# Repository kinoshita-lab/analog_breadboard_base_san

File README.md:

# Analog Breadboard Base san

[日本語](README.ja.md)

You have two cows. You want to build analog circuit with both positive/negative rails...

Here it is!

## Features

- USB PD supported. Use 15V if the PD power source if available
- When not, internal DC-DC can supply 15V(with a limited power which USB port can supply)
  - Confirmed working with M2 Macbook Air and Chuwi Freebook(meaning you can use this board with normal USB type-C port on your PC)
- Has 15V(unregulated) and -15V(unregulated) test point for the convinience of advanced users..

## Kit Contents

- Pre-assembled circuit board
- 2x2 pin socket connector(4 pcs.)
- 2x40 pin socket connector(2 pcs.)
- 2x20 pin socket connector(2 pcs.)

## What you will need

- USB Type-C Adapter(PD 15V supported)
- 2mm flat head screwdriver
- Multimeter

## How to assemble

- Solder the included connectors to the appropriate places on the circuit board.
- Connect USB Type-C adapter to the PCB and adjust both +12 and -12 potentiometer with screwdriver.

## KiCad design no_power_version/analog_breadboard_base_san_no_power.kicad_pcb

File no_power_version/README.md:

# GND Enhanced Breadboard Base chan

[日本語](README.ja.md)

## Kit Contents

- Print circuit board
- 2x2 pin socket connector(4 pcs.)
- 2x40 pin socket connector(2 pcs.)
- 2x20 pin socket connector(2 pcs.)

## What you will need

- Appropriate Power Source

## How to assemble

- Solder the included connectors to the appropriate places on the circuit board.

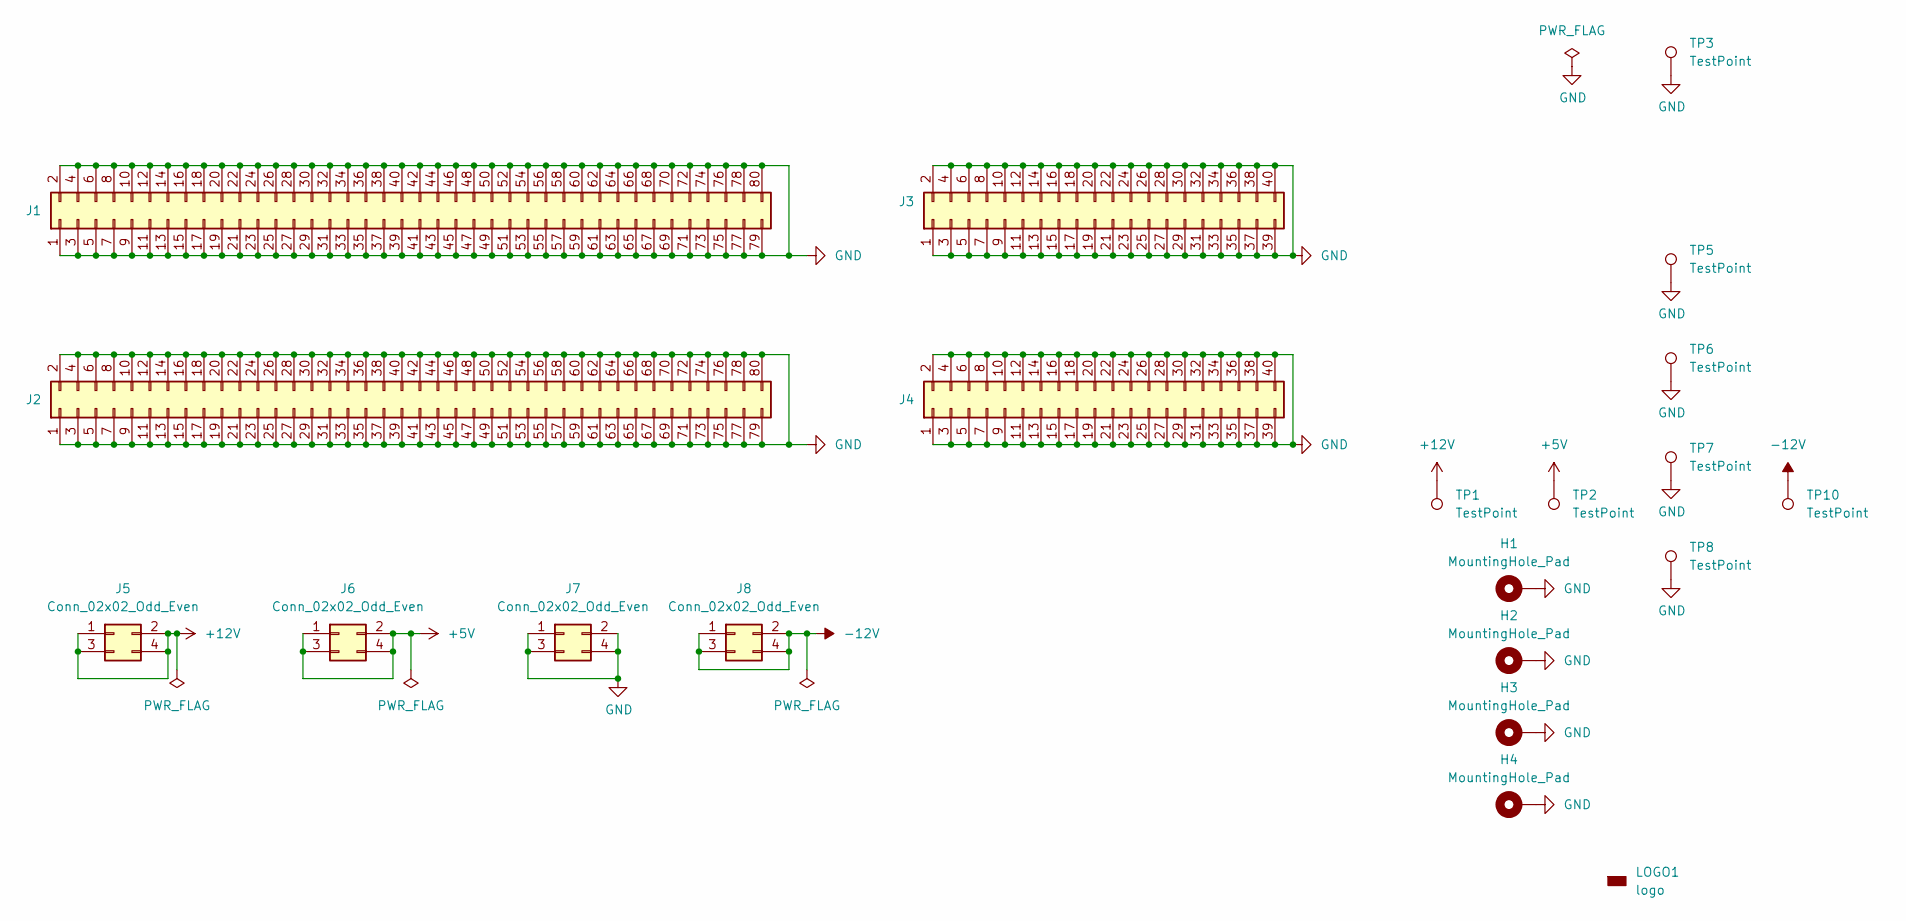
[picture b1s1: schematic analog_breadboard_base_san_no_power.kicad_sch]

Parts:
H1, H2, H3, H4: MountingHole_Pad; MountingHole_3.2mm_M3_DIN965_Pad
J1, J2: Conn_02x40_Odd_Even; PinSocket_2x40_P2.54mm_Vertical; LCSC C343637
J3, J4: Conn_02x20_Odd_Even; PinSocket_2x20_P2.54mm_Vertical; LCSC C2977589
J5, J6, J7, J8: Conn_02x02_Odd_Even; PinSocket_2x02_P2.54mm_Vertical; LCSC C2977590
LOGO1: logo; kinoshita-logo_simplified_300dpi
TP1, TP2, TP3, TP10: TestPoint; TP_PAD_WITH_HOLE
TP5, TP6, TP7, TP8: TestPoint; TP_PAD_LARGE

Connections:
+5V: J6.1, J6.2, J6.3, J6.4, TP2.1
+12V: J5.1, J5.2, J5.3, J5.4, TP1.1
-12V: J8.1, J8.2, J8.3, J8.4, TP10.1
GND: H1.1, H2.1, H3.1, H4.1, J1.1, J1.2, J1.3, J1.4, J1.5, J1.6, J1.7, J1.8, J1.9, J1.10, J1.11, J1.12, J1.13, J1.14, J1.15, J1.16, J1.17, J1.18, J1.19, J1.20, J1.21, J1.22, J1.23, J1.24, J1.25, J1.26, J1.27, J1.28, J1.29, J1.30, J1.31, J1.32, J1.33, J1.34, J1.35, J1.36, J1.37, J1.38, J1.39, J1.40, J1.41, J1.42, J1.43, J1.44, J1.45, J1.46, J1.47, J1.48, J1.49, J1.50, J1.51, J1.52, J1.53, J1.54, J1.55, J1.56, J1.57, J1.58, J1.59, J1.60, J1.61, J1.62, J1.63, J1.64, J1.65, J1.66, J1.67, J1.68, J1.69, J1.70, J1.71, J1.72, J1.73, J1.74, J1.75, J1.76, J1.77, J1.78, J1.79, J1.80, J2.1, J2.2, J2.3, J2.4, J2.5, J2.6, J2.7, J2.8, J2.9, J2.10, J2.11, J2.12, J2.13, J2.14, J2.15, J2.16, J2.17, J2.18, J2.19, J2.20, J2.21, J2.22, J2.23, J2.24, J2.25, J2.26, J2.27, J2.28, J2.29, J2.30, J2.31, J2.32, J2.33, J2.34, J2.35, J2.36, J2.37, J2.38, J2.39, J2.40, J2.41, J2.42, J2.43, J2.44, J2.45, J2.46, J2.47, J2.48, J2.49, J2.50, J2.51, J2.52, J2.53, J2.54, J2.55, J2.56, J2.57, J2.58, J2.59, J2.60, J2.61, J2.62, J2.63, J2.64, J2.65, J2.66, J2.67, J2.68, J2.69, J2.70, J2.71, J2.72, J2.73, J2.74, J2.75, J2.76, J2.77, J2.78, J2.79, J2.80, J3.1, J3.2, J3.3, J3.4, J3.5, J3.6, J3.7, J3.8, J3.9, J3.10, J3.11, J3.12, J3.13, J3.14, J3.15, J3.16, J3.17, J3.18, J3.19, J3.20, J3.21, J3.22, J3.23, J3.24, J3.25, J3.26, J3.27, J3.28, J3.29, J3.30, J3.31, J3.32, J3.33, J3.34, J3.35, J3.36, J3.37, J3.38, J3.39, J3.40, J4.1, J4.2, J4.3, J4.4, J4.5, J4.6, J4.7, J4.8, J4.9, J4.10, J4.11, J4.12, J4.13, J4.14, J4.15, J4.16, J4.17, J4.18, J4.19, J4.20, J4.21, J4.22, J4.23, J4.24, J4.25, J4.26, J4.27, J4.28, J4.29, J4.30, J4.31, J4.32, J4.33, J4.34, J4.35, J4.36, J4.37, J4.38, J4.39, J4.40, J7.1, J7.2, J7.3, J7.4, TP3.1, TP5.1, TP6.1, TP7.1, TP8.1

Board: 2 copper layers, 21 parts (1 on the bottom side), 4 nets, no tracks yet.

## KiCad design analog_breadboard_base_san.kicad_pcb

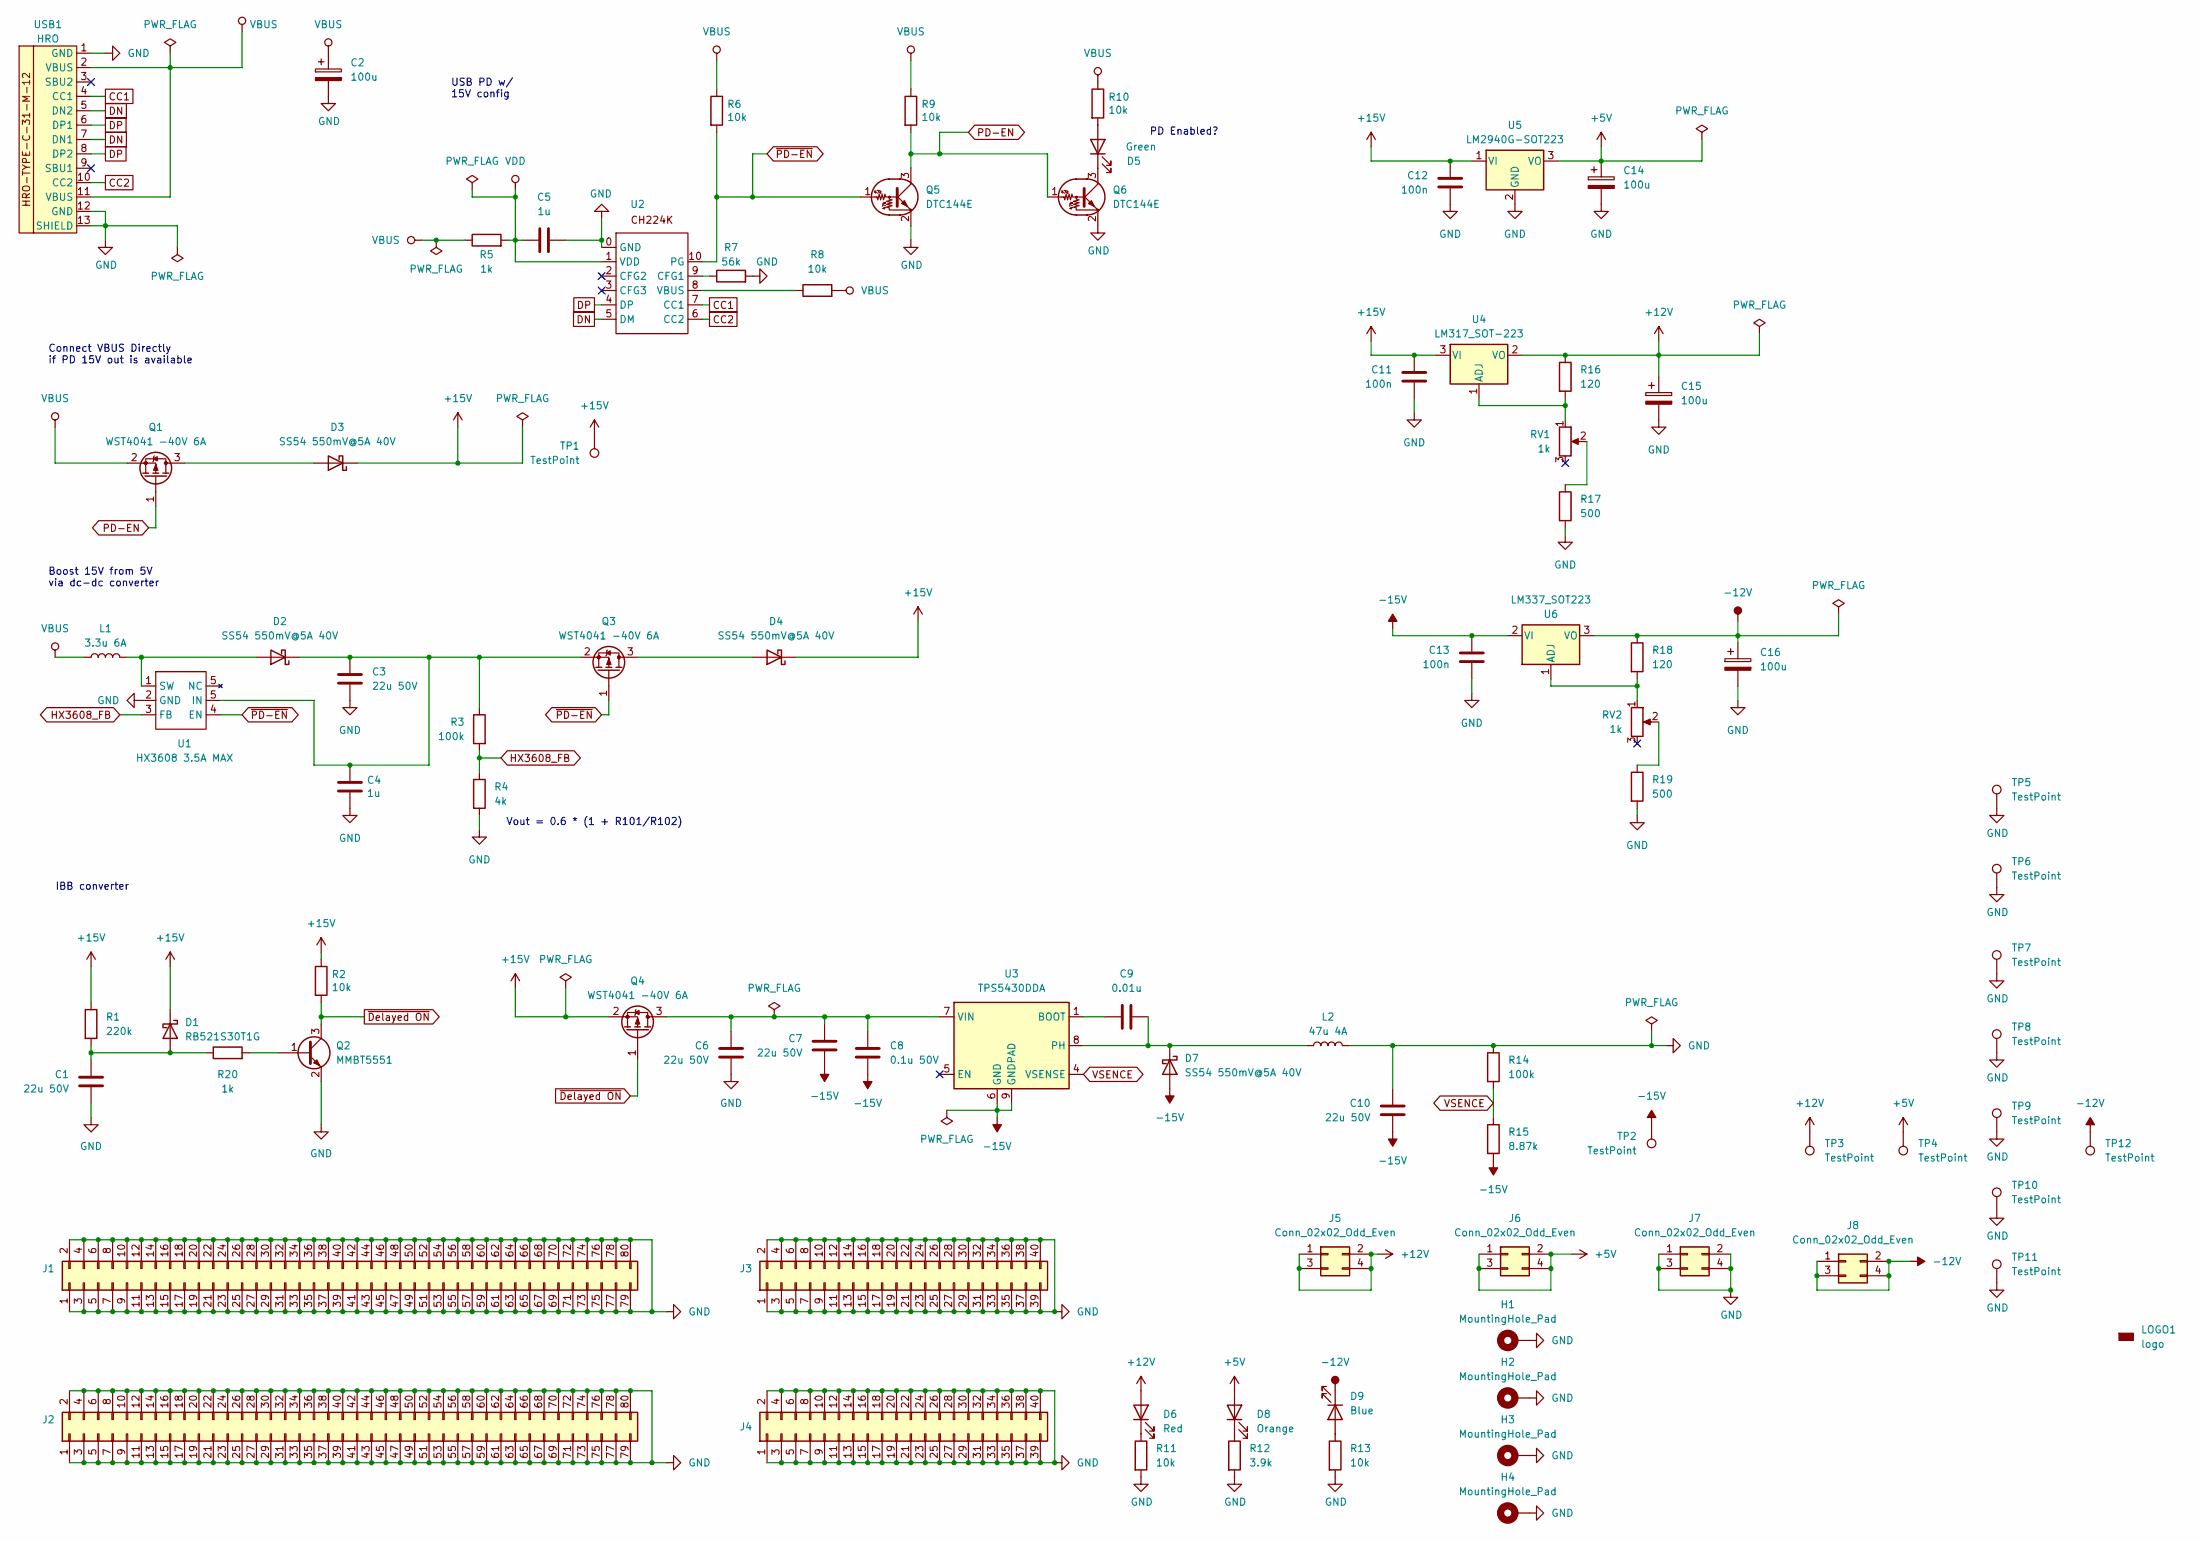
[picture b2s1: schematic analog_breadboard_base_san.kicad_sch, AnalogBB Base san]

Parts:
C1, C6, C7, C10: 22u 50V; C0805; LCSC C22367832
C2, C14, C15, C16: 100u; CP_Elec_6.3x5.4; LCSC C72478
C3: 22u 50V; C0603; LCSC C22367832
C4, C5: 1u; C0402; LCSC C14445
C8: 0.1u 50V; C0603; LCSC C1591
C9: 0.01u; C0603; LCSC C387983
C11, C12, C13: 100n; C0402; LCSC C56392
D1: RB521S30T1G; D_SOD-523; LCSC C145179
D2, D3, D4, D7: SS54 550mV@5A 40V; D_SMA; LCSC C727065
D5: Green; LED_0402_1005Metric_Enhanced_Cathode; LCSC C434449
D6: Red; LED_0402_1005Metric_Enhanced_Cathode; LCSC C434445
D8: Orange; LED_0402_1005Metric_Enhanced_Cathode; LCSC C965791
D9: Blue; LED_0402_1005Metric_Enhanced_Cathode; LCSC C434447
H1, H2, H3, H4: MountingHole_Pad; MountingHole_3.2mm_M3_DIN965_Pad
J1, J2: Conn_02x40_Odd_Even; PinSocket_2x40_P2.54mm_Vertical; LCSC C343637
J3, J4: Conn_02x20_Odd_Even; PinSocket_2x20_P2.54mm_Vertical; LCSC C2977589
J5, J6, J7, J8: Conn_02x02_Odd_Even; PinSocket_2x02_P2.54mm_Vertical; LCSC C2977590
L1: 3.3u 6A; Inductor_SMD_5.2x5.7; LCSC C2847476
L2: 47u 4A; Inductor_SMD_11.5x10.5; LCSC C20415550
LOGO1: logo; kinoshita-logo_simplified_300dpi
Q1, Q3, Q4: WST4041 -40V 6A; SOT-23; LCSC C148357
Q2: MMBT5551; SOT-23; LCSC C2145
Q5, Q6: DTC144E; SOT-523; LCSC C242410
R1: 220k; R_0402_1005Metric; LCSC C25767
R2, R6, R8, R9, R10, R11, R13: 10k; R_0402_1005Metric; LCSC C25744
R3: 100k; R_0402_1005Metric; LCSC C60491
R4: 4k; R_0402_1005Metric; LCSC C51721
R5, R20: 1k; R_0402_1005Metric; LCSC C11702
R7: 56k; R_0402_1005Metric; LCSC C25796
R12: 3.9k; R_0402_1005Metric; LCSC C51721
R14: 100k; R_0402_1005Metric; LCSC C25530
R15: 8.87k; R_0402_1005Metric; LCSC C155696
R16, R18: 120; R_0402_1005Metric; LCSC C25079
R17, R19: 500; R_0402_1005Metric; LCSC C25167
RV1, RV2: 1k; POT_BOCHEN 3296W C118963; LCSC C118949
TP1, TP2, TP3, TP4, TP5, TP12: TestPoint; TP_PAD_WITH_HOLE
TP6, TP7, TP8, TP9, TP10, TP11: TestPoint; TP_PAD_LARGE
U1: HX3608 3.5A MAX; SOT-23-6; LCSC C296278
U2: CH224K; ESSOP-10_3.9x4.9mm_P1.00mm; LCSC C970725
U3: TPS5430DDA; TI_SO-PowerPAD-8_ThermalVias; LCSC C9864
U4: LM317_SOT-223; SOT-223-3_TabPin2; LCSC C347367
U5: LM2940G-SOT223; SOT-223-3_TabPin2; LCSC C71094
U6: LM337_SOT223; SOT-223-3_TabPin2; LCSC C527400
USB1: HRO; Conn USB TYPE-C16P3MDDGP073 C2965608; LCSC C2965608

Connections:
+5V: C14.1, D8.2 (A), J6.1, J6.2, J6.3, J6.4, TP4.1, U5.3 (VO)
+12V: C15.1, D6.2 (A), J5.1, J5.2, J5.3, J5.4, R16.1, TP3.1, U4.2 (VO)
+15V: C11.2, C12.2, D1.1 (K), D3.1 (K), D4.1 (K), Q4.2 (S), R1.1, R2.1, TP1.1, U4.3 (VI), U5.1 (VI)
-12V: C16.1, D9.1 (K), J8.1, J8.2, J8.3, J8.4, R18.1, TP12.1, U6.3 (VO)
-15V: C7.2, C8.1, C10.2, C13.2, D7.2 (A), R15.2, TP2.1, U3.6 (GND), U3.9 (GNDPAD), U6.2 (VI)
CC1: U2.7 (CC1), USB1.4 (CC1)
CC2: U2.6 (CC2), USB1.10 (CC2)
DN: U2.5 (DM), USB1.5 (DN2), USB1.7 (DN1)
DP: U2.4 (DP), USB1.6 (DP1), USB1.8 (DP2)
GND: C1.2, C2.2, C3.2, C4.2, C5.2, C6.2, C10.1, C11.1, C12.1, C13.1, C14.2, C15.2, C16.2, H1.1, H2.1, H3.1, H4.1, J1.1, J1.2, J1.3, J1.4, J1.5, J1.6, J1.7, J1.8, J1.9, J1.10, J1.11, J1.12, J1.13, J1.14, J1.15, J1.16, J1.17, J1.18, J1.19, J1.20, J1.21, J1.22, J1.23, J1.24, J1.25, J1.26, J1.27, J1.28, J1.29, J1.30, J1.31, J1.32, J1.33, J1.34, J1.35, J1.36, J1.37, J1.38, J1.39, J1.40, J1.41, J1.42, J1.43, J1.44, J1.45, J1.46, J1.47, J1.48, J1.49, J1.50, J1.51, J1.52, J1.53, J1.54, J1.55, J1.56, J1.57, J1.58, J1.59, J1.60, J1.61, J1.62, J1.63, J1.64, J1.65, J1.66, J1.67, J1.68, J1.69, J1.70, J1.71, J1.72, J1.73, J1.74, J1.75, J1.76, J1.77, J1.78, J1.79, J1.80, J2.1, J2.2, J2.3, J2.4, J2.5, J2.6, J2.7, J2.8, J2.9, J2.10, J2.11, J2.12, J2.13, J2.14, J2.15, J2.16, J2.17, J2.18, J2.19, J2.20, J2.21, J2.22, J2.23, J2.24, J2.25, J2.26, J2.27, J2.28, J2.29, J2.30, J2.31, J2.32, J2.33, J2.34, J2.35, J2.36, J2.37, J2.38, J2.39, J2.40, J2.41, J2.42, J2.43, J2.44, J2.45, J2.46, J2.47, J2.48, J2.49, J2.50, J2.51, J2.52, J2.53, J2.54, J2.55, J2.56, J2.57, J2.58, J2.59, J2.60, J2.61, J2.62, J2.63, J2.64, J2.65, J2.66, J2.67, J2.68, J2.69, J2.70, J2.71, J2.72, J2.73, J2.74, J2.75, J2.76, J2.77, J2.78, J2.79, J2.80, J3.1, J3.2, J3.3, J3.4, J3.5, J3.6, J3.7, J3.8, J3.9, J3.10, J3.11, J3.12, J3.13, J3.14, J3.15, J3.16, J3.17, J3.18, J3.19, J3.20, J3.21, J3.22, J3.23, J3.24, J3.25, J3.26, J3.27, J3.28, J3.29, J3.30, J3.31, J3.32, J3.33, J3.34, J3.35, J3.36, J3.37, J3.38, J3.39, J3.40, J4.1, J4.2, J4.3, J4.4, J4.5, J4.6, J4.7, J4.8, J4.9, J4.10, J4.11, J4.12, J4.13, J4.14, J4.15, J4.16, J4.17, J4.18, J4.19, J4.20, J4.21, J4.22, J4.23, J4.24, J4.25, J4.26, J4.27, J4.28, J4.29, J4.30, J4.31, J4.32, J4.33, J4.34, J4.35, J4.36, J4.37, J4.38, J4.39, J4.40, J7.1, J7.2, J7.3, J7.4, L2.2, Q2.2 (E), Q5.2 (E), Q6.2 (E), R4.2, R7.2, R11.2, R12.2, R13.2, R14.1, R17.2, R19.2, TP5.1, TP6.1, TP7.1, TP8.1, TP9.1, TP10.1, TP11.1, U1.2 (GND), U2.0 (GND), U5.2 (GND), USB1.1 (GND), USB1.12 (GND), USB1.13 (SHIELD)
HX3608_FB: R3.2, R4.1, U1.3 (FB)
unnamed: C1.1, D1.2 (A), R1.2, R20.1
unnamed: D2.2 (A), L1.2, U1.1 (SW)
unnamed: C3.1, C4.1, D2.1 (K), Q3.2 (S), R3.1, U1.5 (IN)
unnamed: D3.2 (A), Q1.3 (D)
unnamed: D4.2 (A), Q3.3 (D)
unnamed: D5.2 (A), R10.2
unnamed: D5.1 (K), Q6.3 (C)
unnamed: D6.1 (K), R11.1
unnamed: C9.2, D7.1 (K), L2.1, U3.8 (PH)
unnamed: D8.1 (K), R12.1
unnamed: D9.2 (A), R13.1
unnamed: Q2.1 (B), R20.2
unnamed: C6.1, C7.1, C8.2, Q4.3 (D), U3.7 (VIN)
unnamed: R17.1, RV1.2
unnamed: R19.1, RV2.2
unnamed: R7.1, U2.9 (CFG1)
unnamed: R8.1, U2.8 (VBUS)
unnamed: C9.1, U3.1 (BOOT)
unnamed: R16.2, RV1.1, U4.1 (ADJ)
unnamed: R18.2, RV2.1, U6.1 (ADJ)
PD-EN: Q1.1 (G), Q5.3 (C), Q6.1 (B), R9.2
VBUS: C2.1, L1.1, Q1.2 (S), R5.1, R6.1, R8.2, R9.1, R10.1, USB1.2 (VBUS), USB1.11 (VBUS)
VDD: C5.1, R5.2, U2.1 (VDD)
VSENCE: R14.2, R15.1, U3.4 (VSENSE)
~Delayed ON: Q2.3 (C), Q4.1 (G), R2.2
~PD-EN: Q3.1 (G), Q5.1 (B), R6.2, U1.4 (EN), U2.10 (PG)

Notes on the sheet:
IBB converter
USB PD w/ 15V config
Connect VBUS Directly if PD 15V out is available
Vout = 0.6 * (1 + R101/R102)
Boost 15V from 5V via dc-dc converter
PD Enabled?

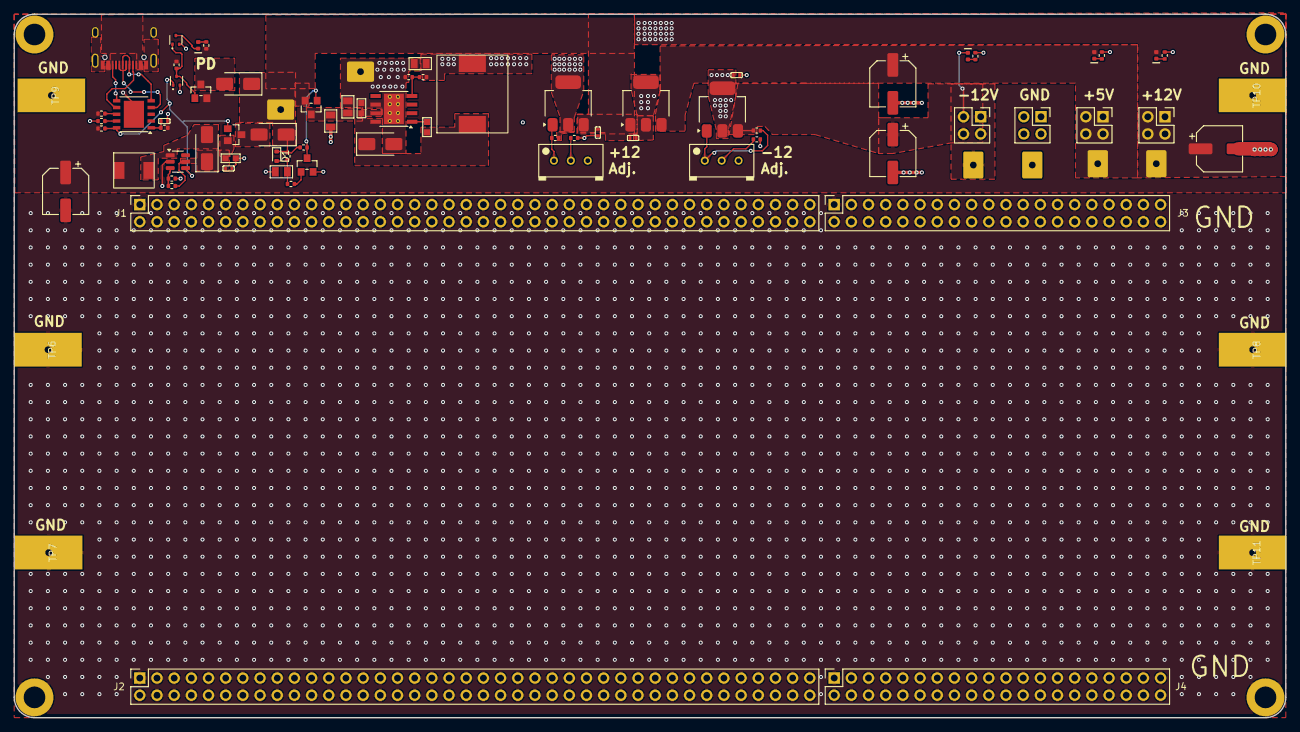
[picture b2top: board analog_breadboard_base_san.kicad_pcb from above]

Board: 2 copper layers, 188.0 x 104.0 mm, 87 parts (1 on the bottom side), 37 nets.

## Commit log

2024-09-17 add some directories
2024-09-19 add kicad files
2024-09-19 add readme
2024-09-20 add how to assemble
2024-09-20 Add doc for no power version
2024-09-20 Create LICENSE
